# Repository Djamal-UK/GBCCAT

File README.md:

# GBCCAT
GBCCAT - Gameboy Color Emulator based on GNUBOY,
still in development, used hardware is ESP32 WROVER chip, ST7789 1.3" LCD 240*240px,
loading games from microSD card, emulator has been controlled by PS2 (USB) keyboard.

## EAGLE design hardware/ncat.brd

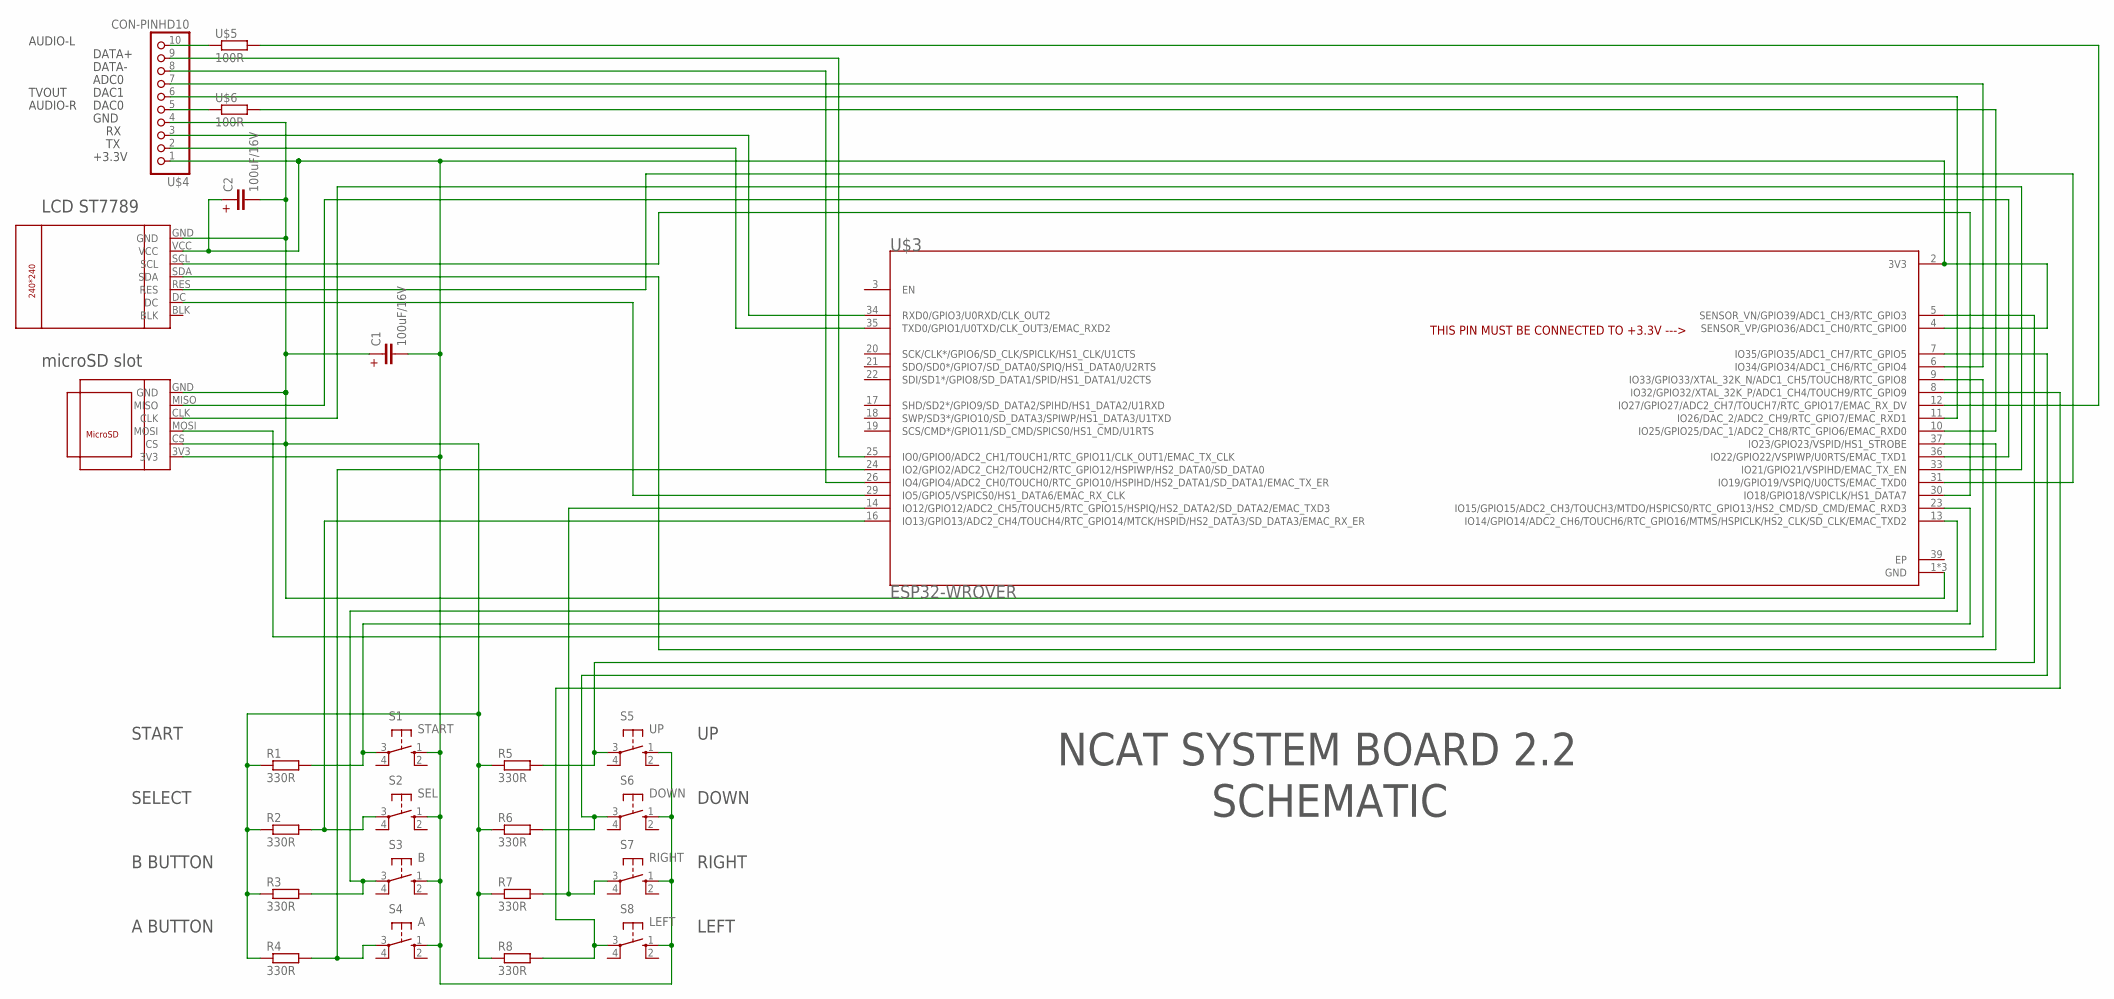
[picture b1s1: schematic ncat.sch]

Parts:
C1, C2: 100uF/16V; C1210
R1, R2, R3, R4, R5, R6, R7, R8: 330R; R0204/5H
S1: START; B3F-10XX
S2: SEL; B3F-10XX
S3: B; B3F-10XX
S4: A; B3F-10XX
S5: UP; B3F-10XX
S6: DOWN; B3F-10XX
S7: RIGHT; B3F-10XX
S8: LEFT; B3F-10XX
U$1: MICROSD-CARD-MODULESMD; MICROSD-CARD-MODULE-SMD
U$3: ESP32-WROVER; XCVR-ESP32-WROVER
U$4: CON-PINHD10; PIN1X10
U$5, U$6: 100R; R1206/SMD
U$7: LCD-ST7789-1.3INCH

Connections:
EP: U$3.39 (EP)
unnamed: U$3.35 (TXD0/GPIO1/U0TXD/CLK_OUT3/EMAC_RXD2), U$4.2
unnamed: U$3.34 (RXD0/GPIO3/U0RXD/CLK_OUT2), U$4.3
unnamed: U$3.12 (IO27/GPIO27/ADC2_CH7/TOUCH7/RTC_GPIO17/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), U$5.2
unnamed: U$4.5, U$6.1
unnamed: U$4.10, U$5.1
unnamed: U$3.11 (IO26/DAC_2/ADC2_CH9/RTC_GPIO7/EMAC_RXD1), U$4.6
unnamed: R8.2, S8.3, U$3.8 (IO32/GPIO32/XTAL_32K_P/ADC1_CH4/TOUCH9/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)
unnamed: R4.2, S4.3, U$3.24 (IO2/GPIO2/ADC2_CH2/TOUCH2/RTC_GPIO12/HS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)
unnamed: U$3.10 (IO25/GPIO25/DAC_1/ADC2_CH8/RTC_GPIO6/EM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), U$6.2
unnamed: U$3.30 (IO18/GPIO18/VSPICLK/HS1_DATA7), U$7.SCL
unnamed: U$3.37 (IO23/GPIO23/VSPID/HS1_STROBE), U$7.SDA
unnamed: U$3.31 (IO19/GPIO19/VSPIQ/U0CTS/EMAC_TXD0), U$7.RES
unnamed: R5.2, S5.3, U$3.5 (SENSOR_VN/GPIO39/ADC1_CH3/RTC_GPIO3)
unnamed: R2.2, S2.3, U$3.16 (IO13/GPIO13/ADC2_CH4/TOUCH4/RTC_GPIO14/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)
unnamed: R3.2, S3.3, U$3.13 (IO14/GPIO14/ADC2_CH6/TOUCH6/RTC_GPIO16/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)
unnamed: U$1.MOSI, U$3.9 (IO33/GPIO33/XTAL_32K_N/ADC1_CH5/TOUCH8/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)
unnamed: U$3.29 (IO5/GPIO5/VSPICS0/HS1_DATA6/EMAC_RX_CLK), U$7.DC
unnamed: U$1.MISO, U$3.36 (IO22/GPIO22/VSPIWP/U0RTS/EMAC_TXD1)
unnamed: U$1.CLK, U$3.33 (IO21/GPIO21/VSPIHD/EMAC_TX_EN)
unnamed: R6.2, S6.3, U$3.7 (IO35/GPIO35/ADC1_CH7/RTC_GPIO5)
unnamed: R1.2, S1.3, U$3.23 (IO15/GPIO15/ADC2_CH3/TOUCH3/MTDO/HSPICS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)
unnamed: U$3.6 (IO34/GPIO34/ADC1_CH6/RTC_GPIO4), U$4.7
unnamed: U$3.26 (IO4/GPIO4/ADC2_CH0/TOUCH0/RTC_GPIO10/HS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), U$4.8
unnamed: U$3.25 (IO0/GPIO0/ADC2_CH1/TOUCH1/RTC_GPIO11/CL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), U$4.9
unnamed: C1.2, C2.1, S1.1 (S), S2.1 (S), S3.1 (S), S4.1 (S), S5.1 (S), S6.1 (S), S7.1 (S), S8.1 (S), U$1.3V3, U$3.2 (3V3), U$3.4 (SENSOR_VP/GPIO36/ADC1_CH0/RTC_GPIO0), U$4.1, U$7.VCC
unnamed: R7.2, S7.3, U$3.14 (IO12/GPIO12/ADC2_CH5/TOUCH5/RTC_GPIO15/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)
unnamed: C1.1, C2.2, R1.1, R2.1, R3.1, R4.1, R5.1, R6.1, R7.1, R8.1, U$1.CS, U$1.GND, U$3.1 (GND), U$3.15 (GND), U$3.38 (GND), U$4.4, U$7.GND

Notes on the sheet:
LCD ST7789
microSD slot
START
SELECT
A BUTTON
B BUTTON
DOWN
RIGHT
LEFT
GND
DAC1
DAC0
ADC0
DATA+
DATA-
+3.3V
SCHEMATIC
TVOUT
AUDIO-L
AUDIO-R
NCAT SYSTEM BOARD 2.2
THIS PIN MUST BE CONNECTED TO +3.3V --->

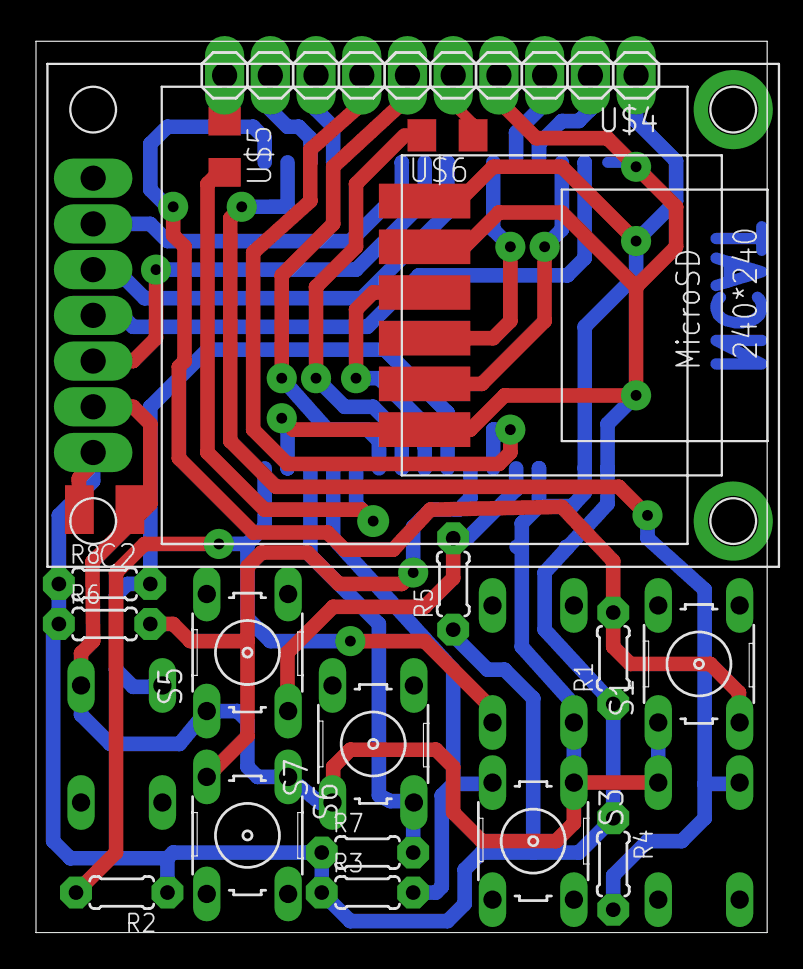
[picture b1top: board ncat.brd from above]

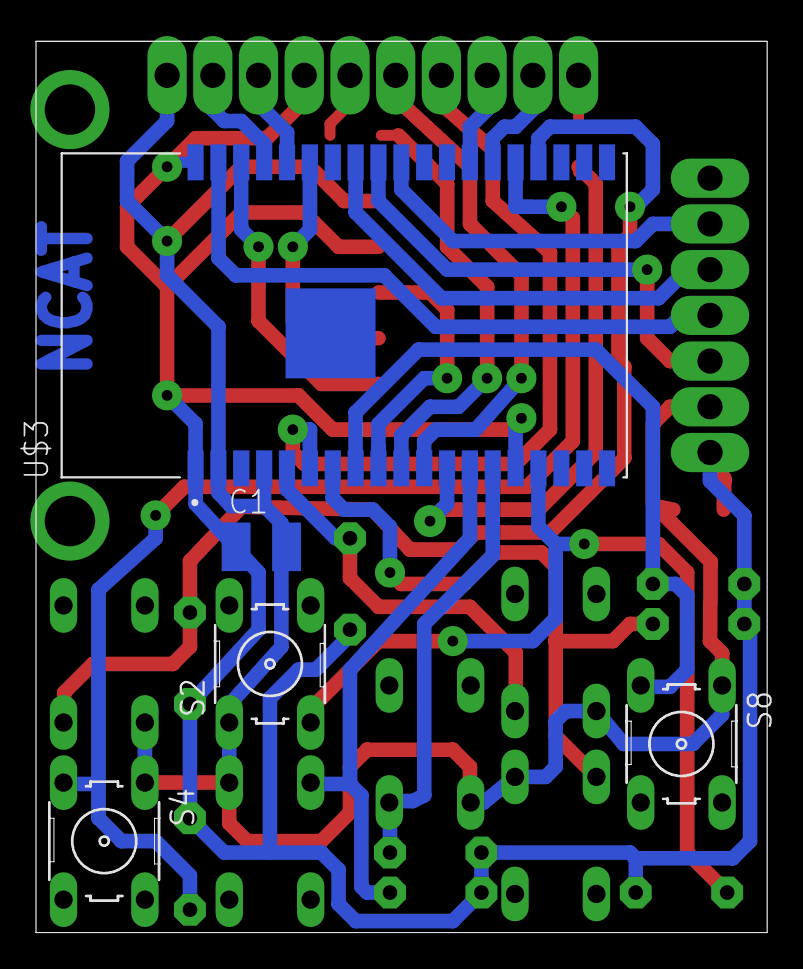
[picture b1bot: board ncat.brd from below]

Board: 2 copper layers, 40.6 x 49.5 mm, 24 parts (5 on the bottom side), 27 nets.

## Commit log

2021-02-03 Initial
2021-02-03 reduce
2021-02-03 adds
2021-02-03 photos
